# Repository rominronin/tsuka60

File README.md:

# tsuka60
Semi-ergo split keyboard

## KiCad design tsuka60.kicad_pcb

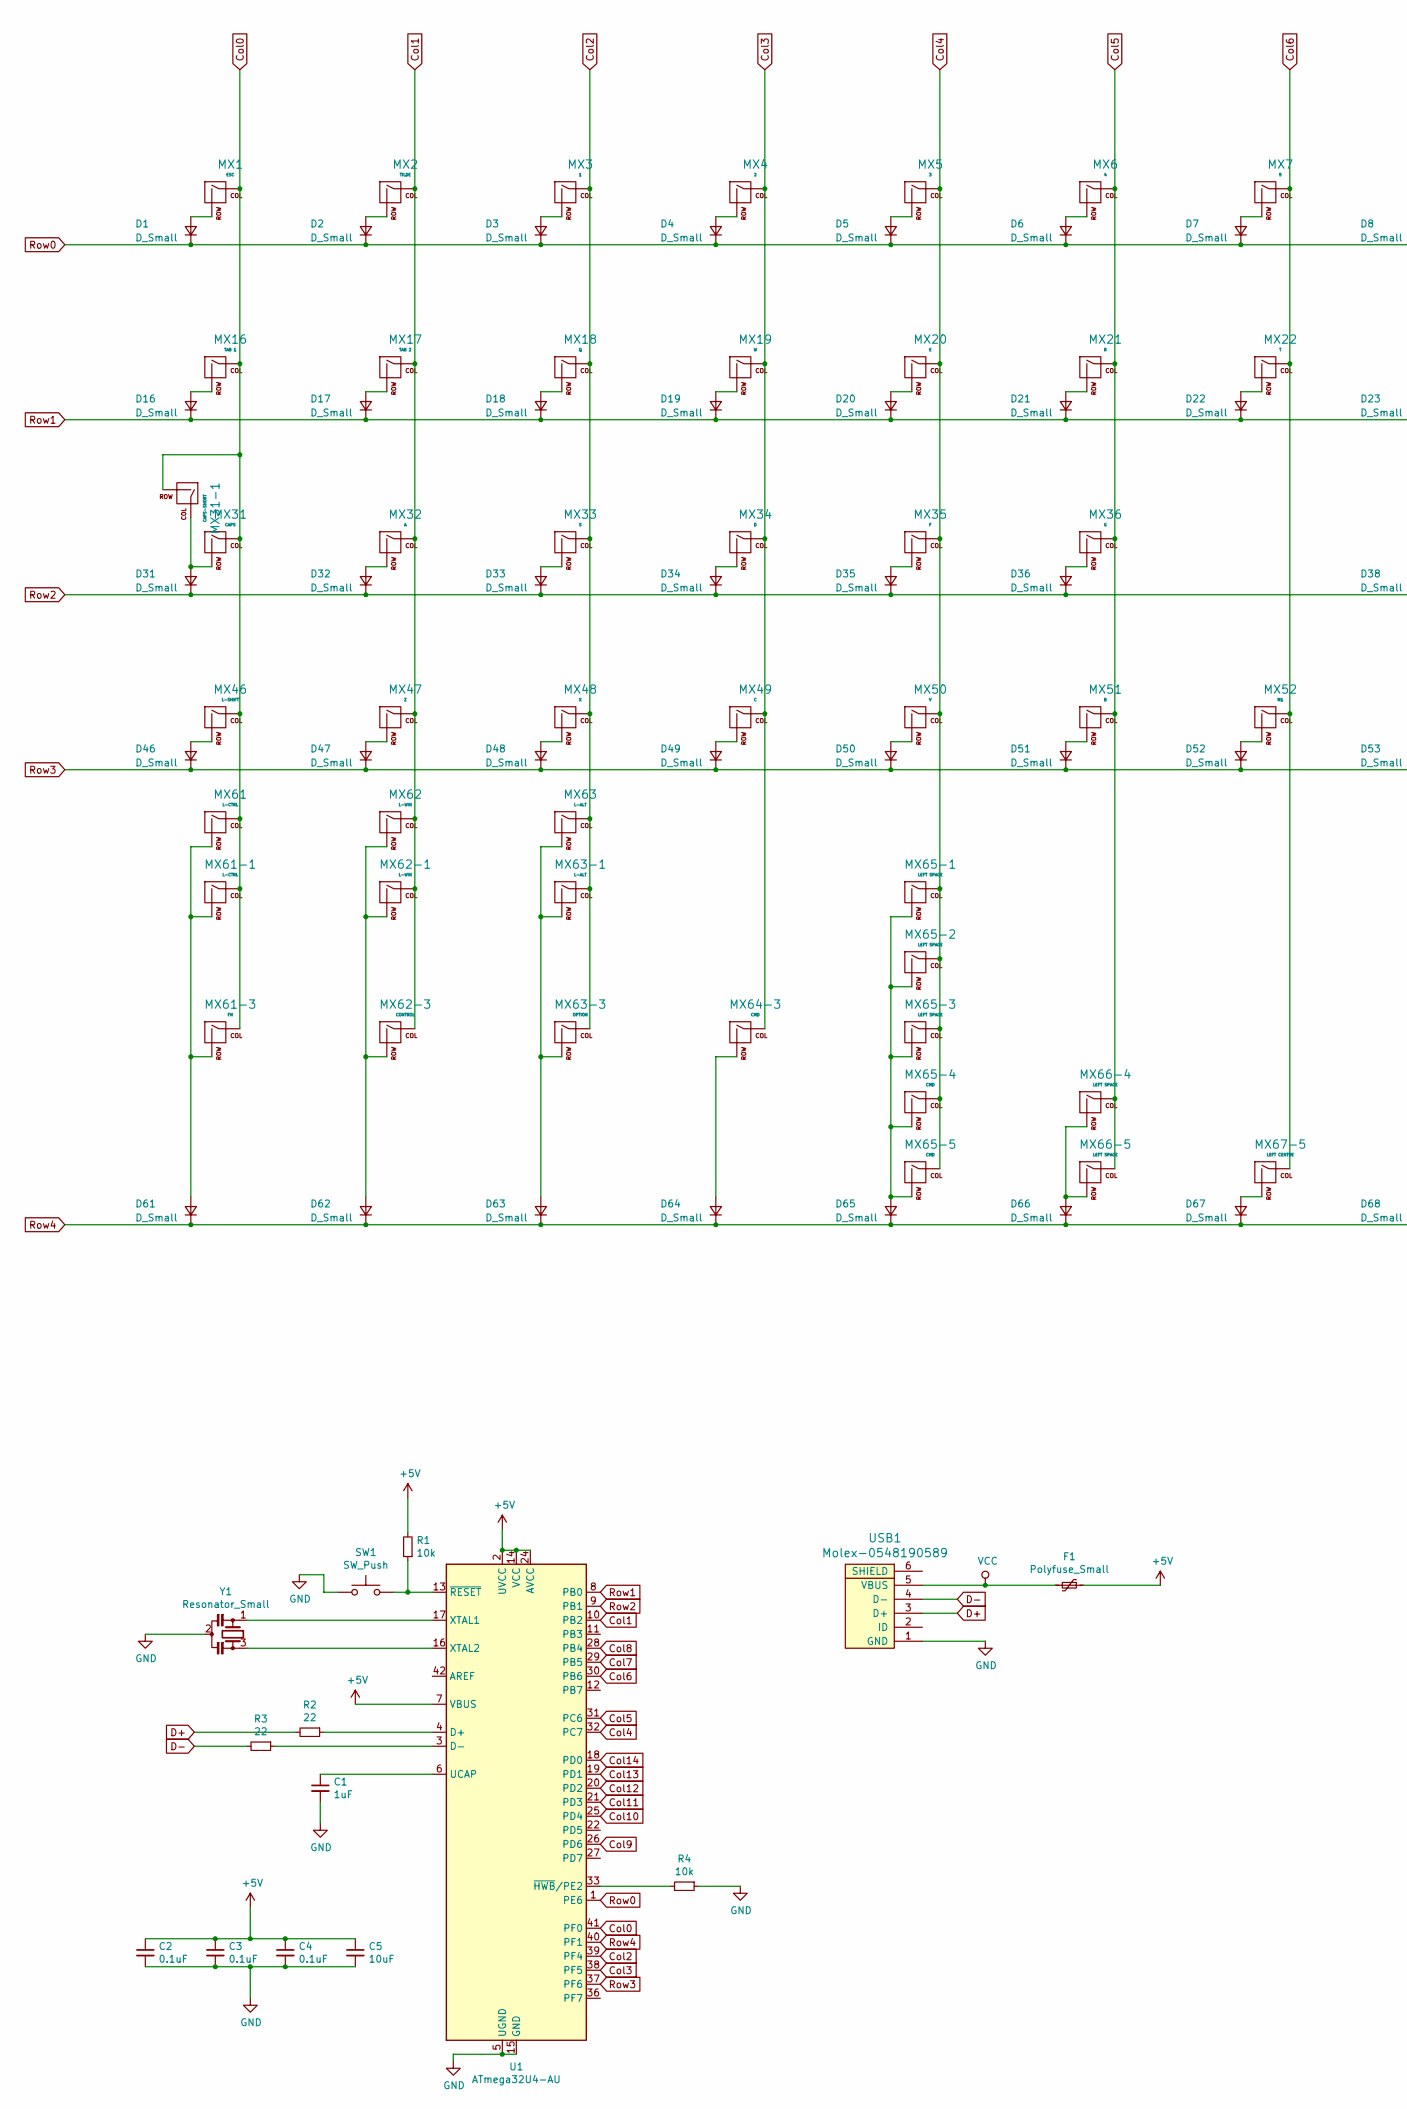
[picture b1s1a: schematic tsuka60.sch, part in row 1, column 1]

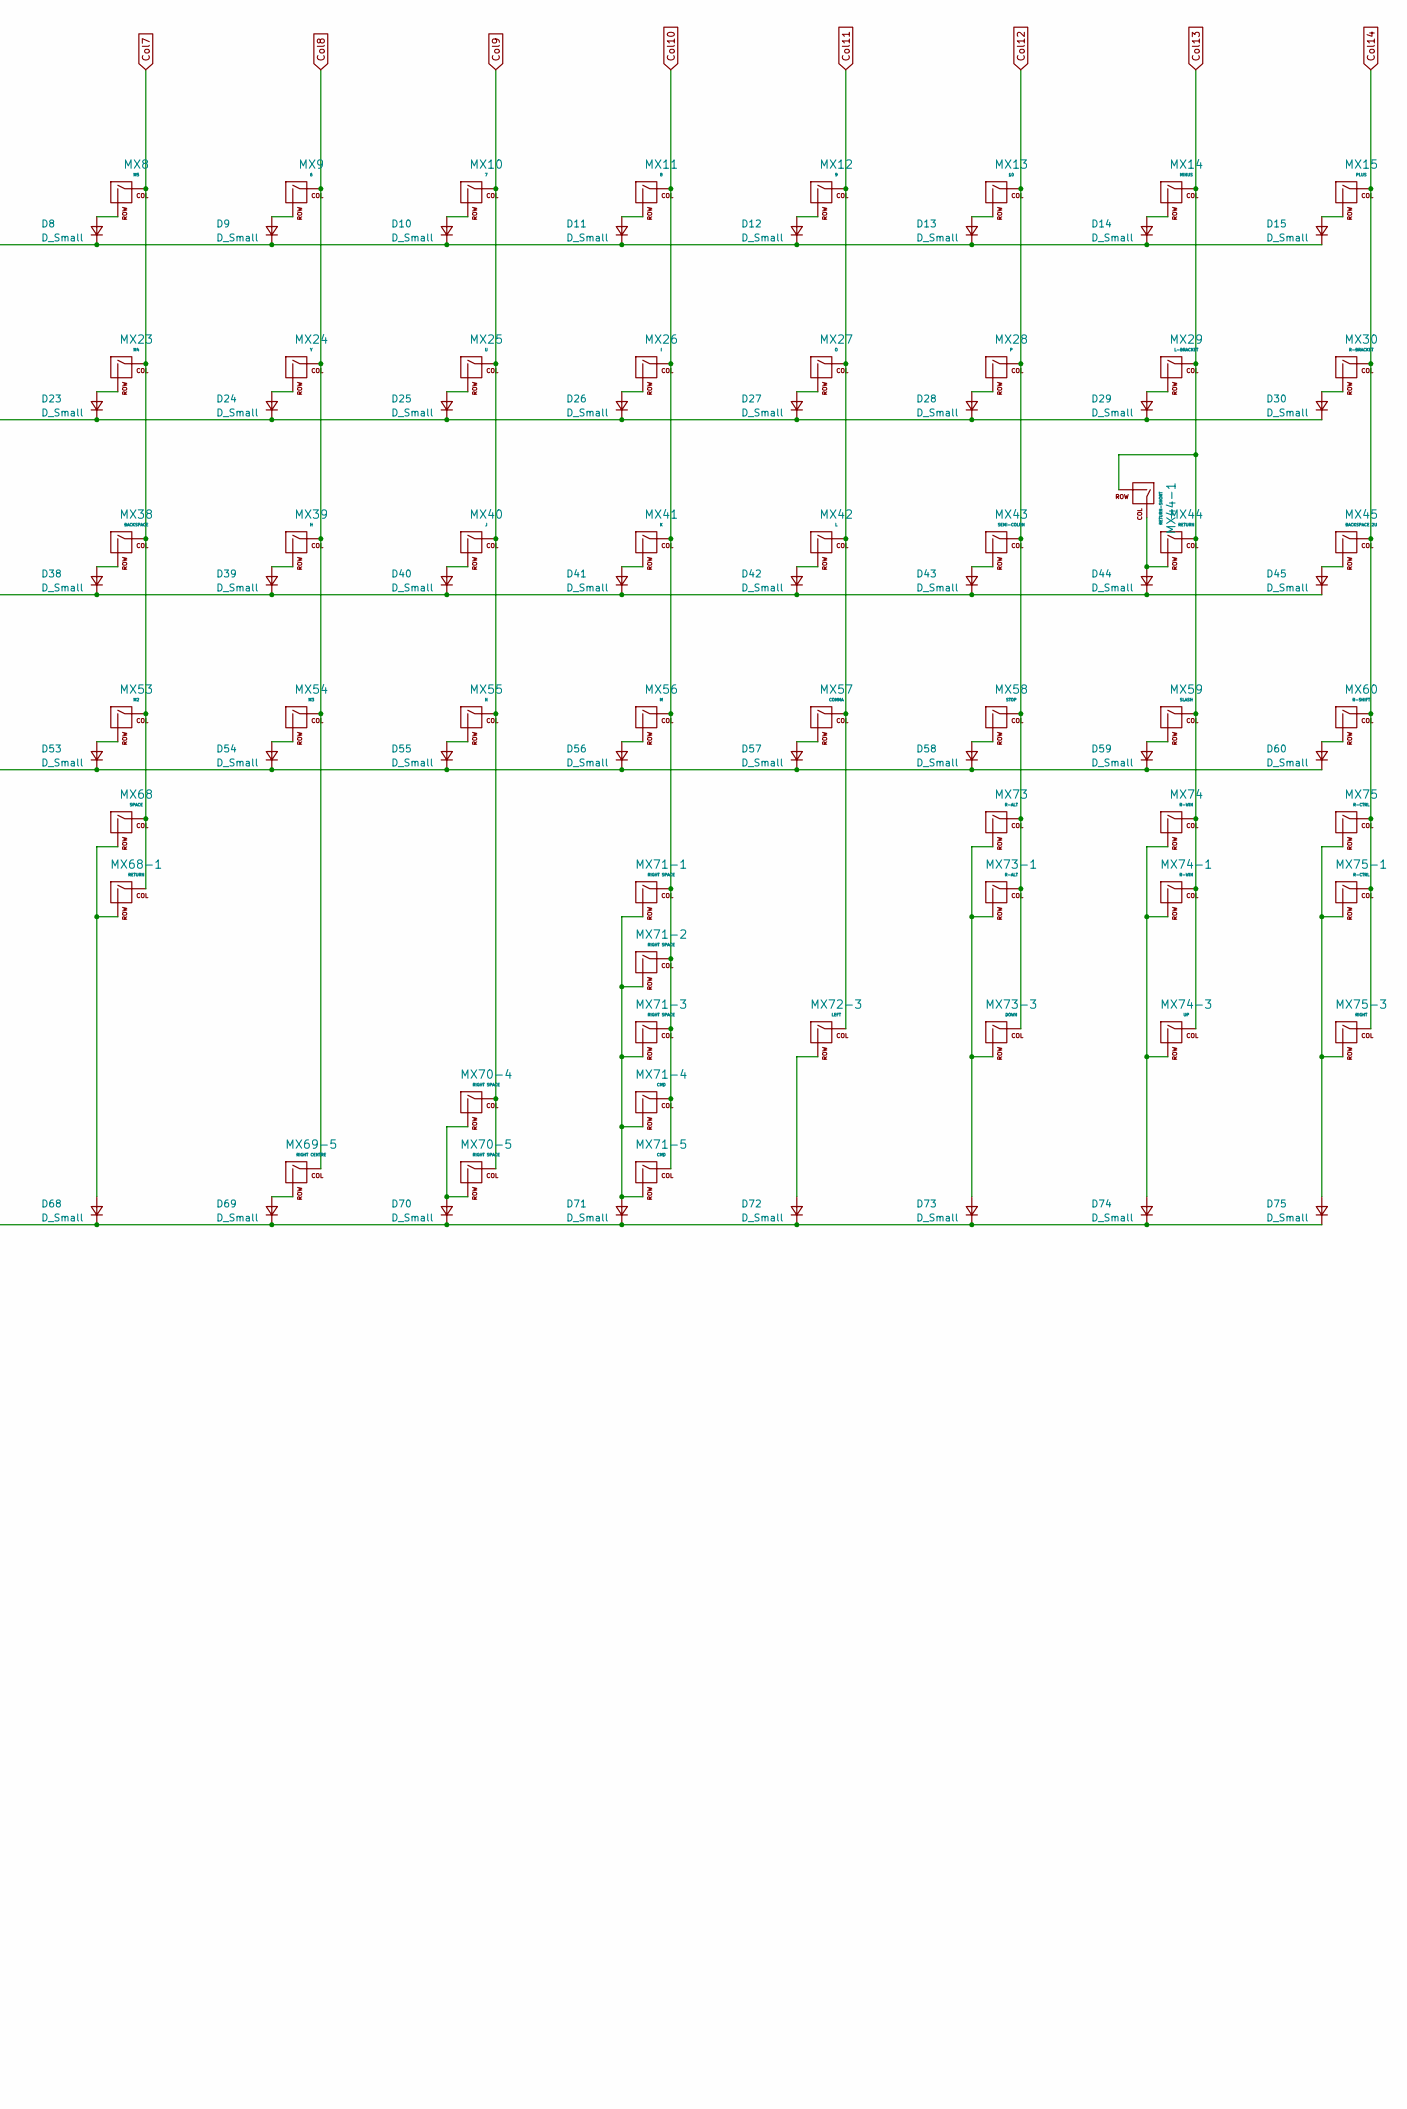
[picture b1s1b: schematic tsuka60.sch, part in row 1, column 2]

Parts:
C1: 1uF; C_0805_2012Metric
C2, C3, C4: 0.1uF; C_0805_2012Metric
C5: 10uF; C_0805_2012Metric
D1, D2, D3, D4, D5, D6, D7, D8, D9, D10, D11, D12, D13, D14, D15, D16, D17, D18, D19, D20, D21, D22, D23, D24, D25, D26, D27, D28, D29, D30, D31, D32, D33, D34, D35, D36, D38, D39, D40, D41, D42, D43, D44, D45, D46, D47, D48, D49, D50, D51, D52, D53, D54, D55, D56, D57, D58, D59, D60, D61, D62, D63, D64, D65, D66, D67, D68, D69, D70, D71, D72, D73, D74, D75: D_Small; D_0805_2012Metric
F1: Polyfuse_Small; Fuse_1206_3216Metric
MX1: ESC; MX-1U-NoLED
MX2: TILDE; MX-1U-NoLED
MX3: 1; MX-1U-NoLED
MX4: 2; MX-1U-NoLED
MX5: 3; MX-1U-NoLED
MX6: 4; MX-1U-NoLED
MX7: 5; MX-1U-NoLED
MX8: M5; MX-1U-NoLED
MX9: 6; MX-1U-NoLED
MX10: 7; MX-1U-NoLED
MX11: 8; MX-1U-NoLED
MX12: 9; MX-1U-NoLED
MX13: 10; MX-1U-NoLED
MX14: MINUS; MX-1U-NoLED
MX15: PLUS; MX-1U-NoLED
MX16: TAB 1; MX-1U-NoLED
MX17: TAB 2; MX-1U-NoLED
MX18: Q; MX-1U-NoLED
MX19: W; MX-1U-NoLED
MX20: E; MX-1U-NoLED
MX21: R; MX-1U-NoLED
MX22: T; MX-1U-NoLED
MX23: M4; MX-1U-NoLED
MX24: Y; MX-1U-NoLED
MX25: U; MX-1U-NoLED
MX26: I; MX-1U-NoLED
MX27: O; MX-1U-NoLED
MX28: P; MX-1U-NoLED
MX29: L-BRACKET; MX-1U-NoLED
MX30: R-BRACKET; MX-1U-NoLED
MX31: CAPS; MX-1.75U-NoLED
MX31-1: CAPS-SHORT; MX-1.25U-NoLED
MX32: A; MX-1U-NoLED
MX33: S; MX-1U-NoLED
MX34: D; MX-1U-NoLED
MX35: F; MX-1U-NoLED
MX36: G; MX-1U-NoLED
MX38: BACKSPACE; MX-1.5U-NoLED
MX39: H; MX-1U-NoLED
MX40: J; MX-1U-NoLED
MX41: K; MX-1U-NoLED
MX42: L; MX-1U-NoLED
MX43: SEMI-COLON; MX-1U-NoLED
MX44: RETURN; MX-1.75U-NoLED
MX44-1: RETURN-SHORT; MX-1.25U-NoLED
MX45: BACKSPACE 2U; MX-2U-NoLED
MX46: L-SHIFT; MX-1.5U-NoLED
MX47: Z; MX-1U-NoLED
MX48: X; MX-1U-NoLED
MX49: C; MX-1U-NoLED
MX50: V; MX-1U-NoLED
MX51: B; MX-1U-NoLED
MX52: M1; MX-1U-NoLED
MX53: M2; MX-2U-ReversedStabilizers-NoLED
MX54: M3; MX-1U-NoLED
MX55: N; MX-1U-NoLED
MX56: M; MX-1U-NoLED
MX57: COMMA; MX-1U-NoLED
MX58: STOP; MX-1U-NoLED
MX59: SLASH; MX-1U-NoLED
MX60: R-SHIFT; MX-1.5U-NoLED
MX61: L-CTRL; MX-1.5U-NoLED
MX61-1: L-CTRL; MX-1.25U-NoLED
MX61-3: FN; MX-1U-NoLED
MX62: L-WIN; MX-1U-NoLED
MX62-1: L-WIN; MX-1.25U-NoLED
MX62-3: CONTROL; MX-1U-NoLED
MX63: L-ALT; MX-1.5U-NoLED
MX63-1: L-ALT; MX-1.25U-NoLED
MX63-3: OPTION; MX-1U-NoLED
MX64-3, MX65-4, MX71-4: CMD; MX-1U-NoLED
MX65-1: LEFT SPACE; MX-2.75U-ReversedStabilizers-NoLED
MX65-2: LEFT SPACE; MX-3U-ReversedStabilizers-NoLED
MX65-3: LEFT SPACE; MX-2.75U-NoLED
MX65-5, MX71-5: CMD; MX-1.25U-NoLED
MX66-4: LEFT SPACE; MX-2U-ReversedStabilizers-NoLED
MX66-5: LEFT SPACE; MX-1.25U-NoLED
MX67-5: LEFT CENTRE; MX-1U-NoLED
MX68: SPACE; MX-7U-ReversedStabilizers-NoLED
MX68-1: RETURN; MX-2U-ReversedStabilizers-NoLED
MX69-5: RIGHT CENTRE; MX-1U-NoLED
MX70-4: RIGHT SPACE; MX-2U-ReversedStabilizers-NoLED
MX70-5: RIGHT SPACE; MX-1.25U-NoLED
MX71-1: RIGHT SPACE; MX-2.75U-ReversedStabilizers-NoLED
MX71-2: RIGHT SPACE; MX-3U-ReversedStabilizers-NoLED
MX71-3: RIGHT SPACE; MX-2.75U-NoLED
MX72-3: LEFT; MX-1U-NoLED
MX73: R-ALT; MX-1.5U-NoLED
MX73-1: R-ALT; MX-1.25U-NoLED
MX73-3: DOWN; MX-1U-NoLED
MX74: R-WIN; MX-1U-NoLED
MX74-1: R-WIN; MX-1.25U-NoLED
MX74-3: UP; MX-1U-NoLED
MX75: R-CTRL; MX-1.5U-NoLED
MX75-1: R-CTRL; MX-1.25U-NoLED
MX75-3: RIGHT; MX-1U-NoLED
R1, R4: 10k; R_0805_2012Metric
R2, R3: 22; R_0805_2012Metric
SW1: SW_Push; SKQG-1155865
U1: ATmega32U4-AU; TQFP-44_10x10mm_P0.8mm
USB1: Molex-0548190589; Molex-0548190519
Y1: Resonator_Small; Resonator_SMD_muRata_CSTxExxV-3Pin_3.0x1.1mm

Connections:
+5V: C2.1, C3.1, C4.1, C5.1, F1.1, R1.2, U1.2 (UVCC), U1.7 (VBUS), U1.14 (VCC), U1.24 (AVCC), U1.34 (VCC), U1.44 (AVCC)
Col0: MX1.1 (COL), MX16.1 (COL), MX31.1 (COL), MX31-1.2 (ROW), MX46.1 (COL), MX61.1 (COL), MX61-1.1 (COL), MX61-3.1 (COL), U1.41 (PF0)
Col1: MX2.1 (COL), MX17.1 (COL), MX32.1 (COL), MX47.1 (COL), MX62.1 (COL), MX62-1.1 (COL), MX62-3.1 (COL), U1.10 (PB2)
Col2: MX3.1 (COL), MX18.1 (COL), MX33.1 (COL), MX48.1 (COL), MX63.1 (COL), MX63-1.1 (COL), MX63-3.1 (COL), U1.39 (PF4)
Col3: MX4.1 (COL), MX19.1 (COL), MX34.1 (COL), MX49.1 (COL), MX64-3.1 (COL), U1.38 (PF5)
Col4: MX5.1 (COL), MX20.1 (COL), MX35.1 (COL), MX50.1 (COL), MX65-1.1 (COL), MX65-2.1 (COL), MX65-3.1 (COL), MX65-4.1 (COL), MX65-5.1 (COL), U1.32 (PC7)
Col5: MX6.1 (COL), MX21.1 (COL), MX36.1 (COL), MX51.1 (COL), MX66-4.1 (COL), MX66-5.1 (COL), U1.31 (PC6)
Col6: MX7.1 (COL), MX22.1 (COL), MX52.1 (COL), MX67-5.1 (COL), U1.30 (PB6)
Col7: MX8.1 (COL), MX23.1 (COL), MX38.1 (COL), MX53.1 (COL), MX68.1 (COL), MX68-1.1 (COL), U1.29 (PB5)
Col8: MX9.1 (COL), MX24.1 (COL), MX39.1 (COL), MX54.1 (COL), MX69-5.1 (COL), U1.28 (PB4)
Col9: MX10.1 (COL), MX25.1 (COL), MX40.1 (COL), MX55.1 (COL), MX70-4.1 (COL), MX70-5.1 (COL), U1.26 (PD6)
Col10: MX11.1 (COL), MX26.1 (COL), MX41.1 (COL), MX56.1 (COL), MX71-1.1 (COL), MX71-2.1 (COL), MX71-3.1 (COL), MX71-4.1 (COL), MX71-5.1 (COL), U1.25 (PD4)
Col11: MX12.1 (COL), MX27.1 (COL), MX42.1 (COL), MX57.1 (COL), MX72-3.1 (COL), U1.21 (PD3)
Col12: MX13.1 (COL), MX28.1 (COL), MX43.1 (COL), MX58.1 (COL), MX73.1 (COL), MX73-1.1 (COL), MX73-3.1 (COL), U1.20 (PD2)
Col13: MX14.1 (COL), MX29.1 (COL), MX44.1 (COL), MX44-1.2 (ROW), MX59.1 (COL), MX74.1 (COL), MX74-1.1 (COL), MX74-3.1 (COL), U1.19 (PD1)
Col14: MX15.1 (COL), MX30.1 (COL), MX45.1 (COL), MX60.1 (COL), MX75.1 (COL), MX75-1.1 (COL), MX75-3.1 (COL), U1.18 (PD0)
D+: R2.2, USB1.3 (D+)
D-: R3.2, USB1.4 (D-)
GND: C1.2, C2.2, C3.2, C4.2, C5.2, R4.1, SW1.1, U1.5 (UGND), U1.15 (GND), U1.23 (GND), U1.35 (GND), U1.43 (GND), USB1.1 (GND), Y1.2
unnamed: C1.1, U1.6 (UCAP)
unnamed: D1.2 (A), MX1.2 (ROW)
unnamed: D2.2 (A), MX2.2 (ROW)
unnamed: D3.2 (A), MX3.2 (ROW)
unnamed: D4.2 (A), MX4.2 (ROW)
unnamed: D5.2 (A), MX5.2 (ROW)
unnamed: D6.2 (A), MX6.2 (ROW)
unnamed: D7.2 (A), MX7.2 (ROW)
unnamed: D8.2 (A), MX8.2 (ROW)
unnamed: D9.2 (A), MX9.2 (ROW)
unnamed: D10.2 (A), MX10.2 (ROW)
unnamed: D11.2 (A), MX11.2 (ROW)
unnamed: D12.2 (A), MX12.2 (ROW)
unnamed: D13.2 (A), MX13.2 (ROW)
unnamed: D14.2 (A), MX14.2 (ROW)
unnamed: D15.2 (A), MX15.2 (ROW)
unnamed: D16.2 (A), MX16.2 (ROW)
unnamed: D17.2 (A), MX17.2 (ROW)
unnamed: D18.2 (A), MX18.2 (ROW)
unnamed: D19.2 (A), MX19.2 (ROW)
unnamed: D20.2 (A), MX20.2 (ROW)
unnamed: D21.2 (A), MX21.2 (ROW)
unnamed: D22.2 (A), MX22.2 (ROW)
unnamed: D23.2 (A), MX23.2 (ROW)
unnamed: D24.2 (A), MX24.2 (ROW)
unnamed: D25.2 (A), MX25.2 (ROW)
unnamed: D26.2 (A), MX26.2 (ROW)
unnamed: D27.2 (A), MX27.2 (ROW)
unnamed: D28.2 (A), MX28.2 (ROW)
unnamed: D29.2 (A), MX29.2 (ROW)
unnamed: D30.2 (A), MX30.2 (ROW)
unnamed: D31.2 (A), MX31.2 (ROW), MX31-1.1 (COL)
unnamed: D32.2 (A), MX32.2 (ROW)
unnamed: D33.2 (A), MX33.2 (ROW)
unnamed: D34.2 (A), MX34.2 (ROW)
unnamed: D35.2 (A), MX35.2 (ROW)
unnamed: D36.2 (A), MX36.2 (ROW)
unnamed: D38.2 (A), MX38.2 (ROW)
unnamed: D39.2 (A), MX39.2 (ROW)
unnamed: D40.2 (A), MX40.2 (ROW)
unnamed: D41.2 (A), MX41.2 (ROW)
unnamed: D42.2 (A), MX42.2 (ROW)
unnamed: D43.2 (A), MX43.2 (ROW)
unnamed: D44.2 (A), MX44.2 (ROW), MX44-1.1 (COL)
unnamed: D45.2 (A), MX45.2 (ROW)
unnamed: D46.2 (A), MX46.2 (ROW)
unnamed: D47.2 (A), MX47.2 (ROW)
unnamed: D48.2 (A), MX48.2 (ROW)
unnamed: D49.2 (A), MX49.2 (ROW)
unnamed: D50.2 (A), MX50.2 (ROW)
unnamed: D51.2 (A), MX51.2 (ROW)
unnamed: D52.2 (A), MX52.2 (ROW)
unnamed: D53.2 (A), MX53.2 (ROW)
unnamed: D54.2 (A), MX54.2 (ROW)
unnamed: D55.2 (A), MX55.2 (ROW)
unnamed: D56.2 (A), MX56.2 (ROW)
unnamed: D57.2 (A), MX57.2 (ROW)
unnamed: D58.2 (A), MX58.2 (ROW)
unnamed: D59.2 (A), MX59.2 (ROW)
unnamed: D60.2 (A), MX60.2 (ROW)
unnamed: D61.2 (A), MX61.2 (ROW), MX61-1.2 (ROW), MX61-3.2 (ROW)
unnamed: D62.2 (A), MX62.2 (ROW), MX62-1.2 (ROW), MX62-3.2 (ROW)
unnamed: D63.2 (A), MX63.2 (ROW), MX63-1.2 (ROW), MX63-3.2 (ROW)
unnamed: D64.2 (A), MX64-3.2 (ROW)
unnamed: D65.2 (A), MX65-1.2 (ROW), MX65-2.2 (ROW), MX65-3.2 (ROW), MX65-4.2 (ROW), MX65-5.2 (ROW)
unnamed: D66.2 (A), MX66-4.2 (ROW), MX66-5.2 (ROW)
unnamed: D67.2 (A), MX67-5.2 (ROW)
unnamed: D68.2 (A), MX68.2 (ROW), MX68-1.2 (ROW)
unnamed: D69.2 (A), MX69-5.2 (ROW)
unnamed: D70.2 (A), MX70-4.2 (ROW), MX70-5.2 (ROW)
unnamed: D71.2 (A), MX71-1.2 (ROW), MX71-2.2 (ROW), MX71-3.2 (ROW), MX71-4.2 (ROW), MX71-5.2 (ROW)
unnamed: D72.2 (A), MX72-3.2 (ROW)
unnamed: D73.2 (A), MX73.2 (ROW), MX73-1.2 (ROW), MX73-3.2 (ROW)
unnamed: D74.2 (A), MX74.2 (ROW), MX74-1.2 (ROW), MX74-3.2 (ROW)
unnamed: D75.2 (A), MX75.2 (ROW), MX75-1.2 (ROW), MX75-3.2 (ROW)
unnamed: R1.1, SW1.2, U1.13 (~RESET)
unnamed: R2.1, U1.4 (D+)
unnamed: R3.1, U1.3 (D-)
unnamed: R4.2, U1.33 (~HWB~/PE2)
unnamed: U1.16 (XTAL2), Y1.3
unnamed: U1.17 (XTAL1), Y1.1
Row0: D1.1 (K), D2.1 (K), D3.1 (K), D4.1 (K), D5.1 (K), D6.1 (K), D7.1 (K), D8.1 (K), D9.1 (K), D10.1 (K), D11.1 (K), D12.1 (K), D13.1 (K), D14.1 (K), D15.1 (K), U1.1 (PE6)
Row1: D16.1 (K), D17.1 (K), D18.1 (K), D19.1 (K), D20.1 (K), D21.1 (K), D22.1 (K), D23.1 (K), D24.1 (K), D25.1 (K), D26.1 (K), D27.1 (K), D28.1 (K), D29.1 (K), D30.1 (K), U1.8 (PB0)
Row2: D31.1 (K), D32.1 (K), D33.1 (K), D34.1 (K), D35.1 (K), D36.1 (K), D38.1 (K), D39.1 (K), D40.1 (K), D41.1 (K), D42.1 (K), D43.1 (K), D44.1 (K), D45.1 (K), U1.9 (PB1)
Row3: D46.1 (K), D47.1 (K), D48.1 (K), D49.1 (K), D50.1 (K), D51.1 (K), D52.1 (K), D53.1 (K), D54.1 (K), D55.1 (K), D56.1 (K), D57.1 (K), D58.1 (K), D59.1 (K), D60.1 (K), U1.37 (PF6)
Row4: D61.1 (K), D62.1 (K), D63.1 (K), D64.1 (K), D65.1 (K), D66.1 (K), D67.1 (K), D68.1 (K), D69.1 (K), D70.1 (K), D71.1 (K), D72.1 (K), D73.1 (K), D74.1 (K), D75.1 (K), U1.40 (PF1)
VCC: F1.2, USB1.5 (VBUS)

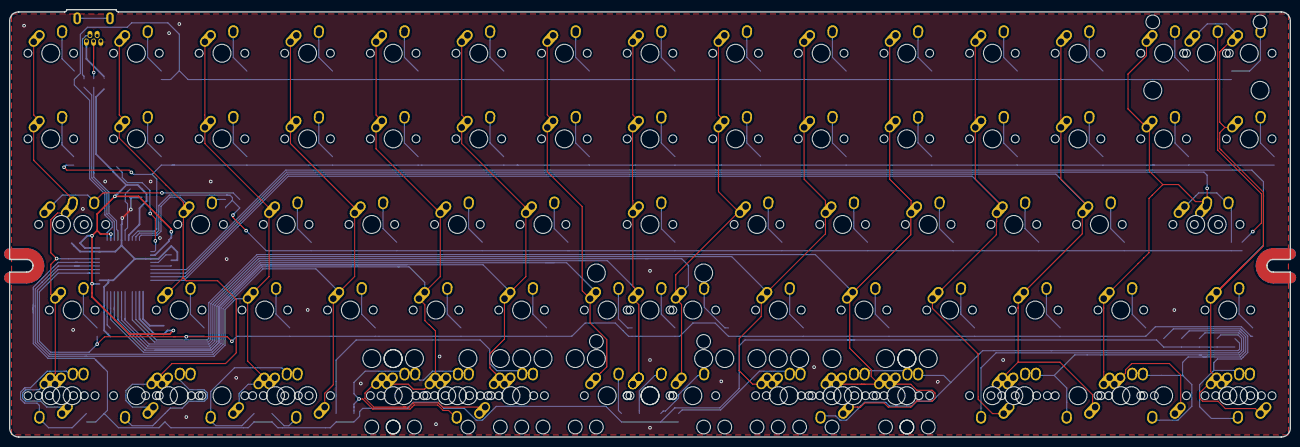
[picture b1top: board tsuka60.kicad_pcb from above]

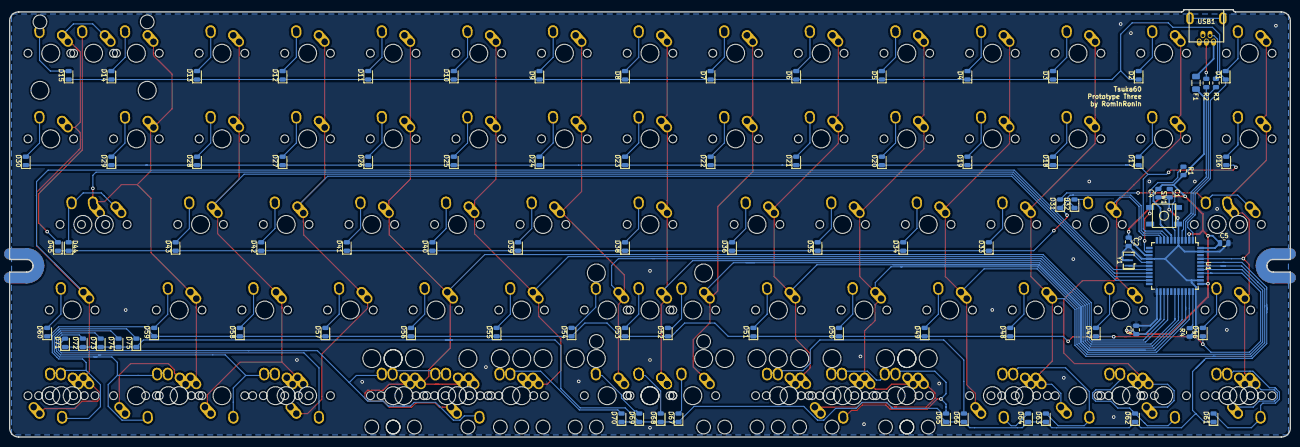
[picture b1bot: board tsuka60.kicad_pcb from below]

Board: 2 copper layers, 285.0 x 95.1 mm, 187 parts (88 on the bottom side), 106 nets.

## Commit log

2019-09-14 new project
2019-09-14 Added library submodules
2019-09-14 added libraries to the project
2019-09-14 Laid out schematic (no switches yet)
2019-09-14 basic matrix layout complete
2019-09-14 assigned footprints and generated netlist
2019-09-14 Started component layout
2019-09-14 Started organising bottom rows
2019-09-14 Start with the layout of diodes
2019-09-14 ready for tracing
2019-09-14 started tracing
2019-09-15 tracing
2019-09-17 more traces
2019-10-11 more tracing
2019-10-11 completed all traces
2019-10-11 finish traces and fixed bugs
2019-10-15 retraced around stabiliser cutouts
2019-10-15 Added double ground fills
2019-10-15 added label
2019-10-15 Prototype One
2019-10-15 gerber settings
2019-10-31 Fixed broken traces
2019-11-19 updated the schematic
2019-11-19 updated schematic and PCB
2019-11-27 updated the routing
2019-11-30 fixed bug errors
2019-11-30 more improvements
2020-02-01 updated the pcb layout
2020-02-01 fixed broken trace
2020-02-01 Prototype two
2020-04-13 added two new 2.75u footprints for ALPS compatibility
2020-04-13 Added alternative right-shift keys
2020-04-13 updated the edge cuts layer
2020-04-13 removed lots of compatibility
2020-04-13 updated the PCB to better accommodate ALPS switches
2020-04-13 Adjusted bottom row. Need to add a new bottom row for the Colemak Forum people.
2020-04-16 restructured the bottom rows
2020-04-18 Traced routes for the new layouts, improved much of the other tracing
2020-04-18 adjusted the visible layers
2020-04-18 last save before exporting gerbers
2020-04-18 Exported gerber files for prototype 3
